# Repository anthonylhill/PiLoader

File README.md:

# PiZero Adapter for Lee Hart's Membership Card
### Project Web Page :  [ http://anthonylhill.github.io ](http://anthonylhill.github.io)
<table> 
    <tr>
        <td>System</td><td>Lee Hart's Membership Card</td>
    </tr>    
    <tr>
        <td>Processor</td><td>CDP1802 1.8 or 4 MHz</td>
    </tr>
    <tr>
        <td>Raspberry Pi</td><td>Zero,  Zero W, Zero 2 W</td>
    </tr>
    <tr>
        <td>Software</td><td>1802 Loader Program</td>
    </tr>
</table>

Software README.TXT :   https://github.com/anthonylhill/PiLoader/blob/main/Software/README.TXT </br>
<B>Tags</B> : CDP1802 eclectic retro mishmash fusion retro-futurism anachronism

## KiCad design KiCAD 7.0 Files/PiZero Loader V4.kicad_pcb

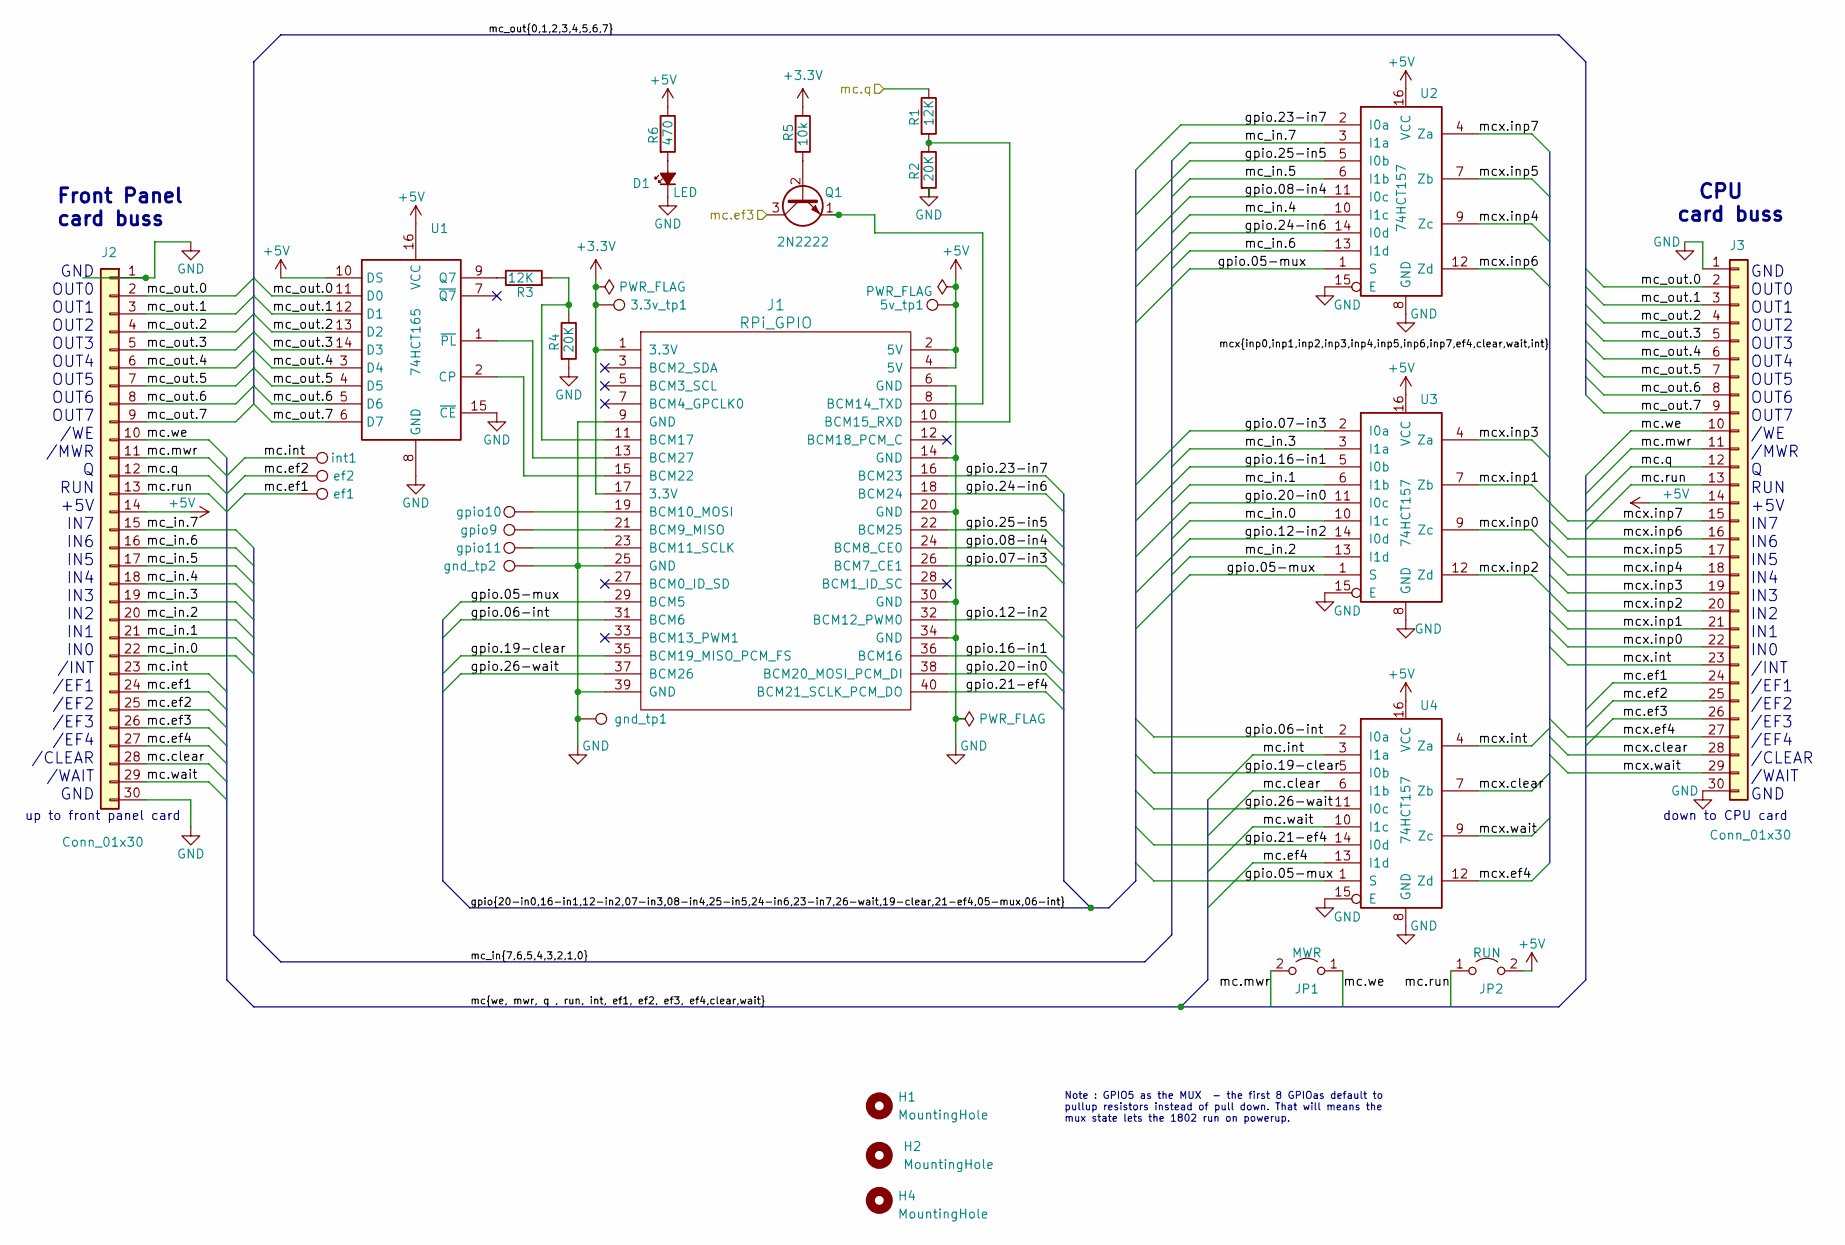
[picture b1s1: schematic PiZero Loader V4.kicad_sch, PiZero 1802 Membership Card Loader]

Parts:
3.3v_tp1, 5v_tp1: TestPoint; TestPoint_THTPad_D2.0mm_Drill1.0mm
D1: LED; PinHeader_1x02_P2.54mm_Vertical
H1, H2, H4: MountingHole; MountingHole_3.2mm_M3
J1: RPi_GPIO; Raspberry_Pi_Zero_Socketed_THT_FaceDown_MountingHoles
J2: Conn_01x30; PinHeader_1x30_P2.54mm_Vertical
J3: Conn_01x30; PinSocket_1x30_P2.54mm_Vertical
JP1: MWR; PinHeader_1x02_P2.54mm_Vertical
JP2: RUN; PinHeader_1x02_P2.54mm_Vertical
Q1: 2N2222; TO-92_Inline
R1, R3: 12K; R_Axial_DIN0207_L6.3mm_D2.5mm_P10.16mm_Horizontal
R2, R4: 20K; R_Axial_DIN0207_L6.3mm_D2.5mm_P10.16mm_Horizontal
R5: 10k; R_Axial_DIN0207_L6.3mm_D2.5mm_P10.16mm_Horizontal
R6: 470; R_Axial_DIN0207_L6.3mm_D2.5mm_P10.16mm_Horizontal
U1: 74HCT165; DIP-16_W7.62mm_Socket
U2, U3, U4: 74HCT157; DIP-16_W7.62mm_Socket
ef1, ef2: TestPoint; TestPoint_THTPad_D2.0mm_Drill1.0mm
gnd_tp1: TestPoint; TestPoint_THTPad_D2.0mm_Drill1.0mm
gnd_tp2: TestPoint; TestPoint_THTPad_2.0x2.0mm_Drill1.0mm
gpio9, gpio10, gpio11: TestPoint; TestPoint_THTPad_D2.0mm_Drill1.0mm
int1: TestPoint; TestPoint_THTPad_D2.0mm_Drill1.0mm

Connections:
+3.3V: 3.3v_tp1.1, J1.1 (3.3V), J1.17 (3.3V), R5.2
+5V: 5v_tp1.1, J1.2 (5V), J1.4 (5V), J2.14, J3.14, JP2.2 (B), R6.1, U1.10 (DS), U1.16 (VCC), U2.16 (VCC), U3.16 (VCC), U4.16 (VCC)
/gpio.05-mux: J1.29 (BCM5), U2.1 (S), U3.1 (S), U4.1 (S)
/gpio.06-int: J1.31 (BCM6), U4.2 (I0a)
/gpio.07-in3: J1.26 (BCM7_CE1), U3.2 (I0a)
/gpio.08-in4: J1.24 (BCM8_CE0), U2.11 (I0c)
/gpio.12-in2: J1.32 (BCM12_PWM0), U3.14 (I0d)
/gpio.16-in1: J1.36 (BCM16), U3.5 (I0b)
/gpio.19-clear: J1.35 (BCM19_MISO_PCM_FS), U4.5 (I0b)
/gpio.20-in0: J1.38 (BCM20_MOSI_PCM_DI), U3.11 (I0c)
/gpio.21-ef4: J1.40 (BCM21_SCLK_PCM_DO), U4.14 (I0d)
/gpio.23-in7: J1.16 (BCM23), U2.2 (I0a)
/gpio.24-in6: J1.18 (BCM24), U2.14 (I0d)
/gpio.25-in5: J1.22 (BCM25), U2.5 (I0b)
/gpio.26-wait: J1.37 (BCM26), U4.11 (I0c)
/mc.clear: J2.28, U4.6 (I1b)
/mc.ef1: J2.24, J3.24, ef1.1
/mc.ef2: J2.25, J3.25, ef2.1
/mc.ef3: J2.26, J3.26, Q1.3 (C)
/mc.ef4: J2.27, U4.13 (I1d)
/mc.int: J2.23, U4.3 (I1a), int1.1
/mc.mwr: J2.11, J3.11, JP1.2 (B)
/mc.q: J2.12, J3.12, R1.1
/mc.run: J2.13, J3.13, JP2.1 (A)
/mc.wait: J2.29, U4.10 (I1c)
/mc.we: J2.10, J3.10, JP1.1 (A)
/mc_in.0: J2.22, U3.10 (I1c)
/mc_in.1: J2.21, U3.6 (I1b)
/mc_in.2: J2.20, U3.13 (I1d)
/mc_in.3: J2.19, U3.3 (I1a)
/mc_in.4: J2.18, U2.10 (I1c)
/mc_in.5: J2.17, U2.6 (I1b)
/mc_in.6: J2.16, U2.13 (I1d)
/mc_in.7: J2.15, U2.3 (I1a)
/mc_out.0: J2.2, J3.2, U1.11 (D0)
/mc_out.1: J2.3, J3.3, U1.12 (D1)
/mc_out.2: J2.4, J3.4, U1.13 (D2)
/mc_out.3: J2.5, J3.5, U1.14 (D3)
/mc_out.4: J2.6, J3.6, U1.3 (D4)
/mc_out.5: J2.7, J3.7, U1.4 (D5)
/mc_out.6: J2.8, J3.8, U1.5 (D6)
/mc_out.7: J2.9, J3.9, U1.6 (D7)
/mcx.clear: J3.28, U4.7 (Zb)
/mcx.ef4: J3.27, U4.12 (Zd)
/mcx.inp0: J3.22, U3.9 (Zc)
/mcx.inp1: J3.21, U3.7 (Zb)
/mcx.inp2: J3.20, U3.12 (Zd)
/mcx.inp3: J3.19, U3.4 (Za)
/mcx.inp4: J3.18, U2.9 (Zc)
/mcx.inp5: J3.17, U2.7 (Zb)
/mcx.inp6: J3.16, U2.12 (Zd)
/mcx.inp7: J3.15, U2.4 (Za)
/mcx.int: J3.23, U4.4 (Za)
/mcx.wait: J3.29, U4.9 (Zc)
GND: D1.1 (K), J1.6 (GND), J1.9 (GND), J1.14 (GND), J1.20 (GND), J1.25 (GND), J1.30 (GND), J1.34 (GND), J1.39 (GND), J2.1, J2.30, J3.1, J3.30, R2.2, R4.2, U1.8 (GND), U1.15 (~CE), U2.8 (GND), U2.15 (E), U3.8 (GND), U3.15 (E), U4.8 (GND), U4.15 (E), gnd_tp1.1, gnd_tp2.1
unnamed: D1.2 (A), R6.2
unnamed: J1.21 (BCM9_MISO), gpio9.1
unnamed: J1.19 (BCM10_MOSI), gpio10.1
unnamed: J1.23 (BCM11_SCLK), gpio11.1
unnamed: J1.8 (BCM14_TXD), Q1.1 (E)
unnamed: J1.10 (BCM15_RXD), R1.2, R2.1
unnamed: J1.11 (BCM17), R3.2, R4.1
unnamed: J1.15 (BCM22), U1.2 (CP)
unnamed: J1.13 (BCM27), U1.1 (~PL)
unnamed: Q1.2 (B), R5.1
unnamed: R3.1, U1.9 (Q7)

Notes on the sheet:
Front Panel card buss
GND OUT0 OUT1 OUT2 OUT3 OUT4 OUT5 OUT6 OUT7 /WE /MWR Q RUN +5V IN7 IN6 IN5 IN4 IN3 IN2 IN1 IN0 /INT /EF1 /EF2 /EF3 /EF4 /CLEAR /WAIT GND
Note : GPIO5 as the MUX - the first 8 GPIOas default to pullup resistors instead of pull down. That will means the mux state lets the 1802 run on powerup.
CPU card buss
up to front panel card
down to CPU card

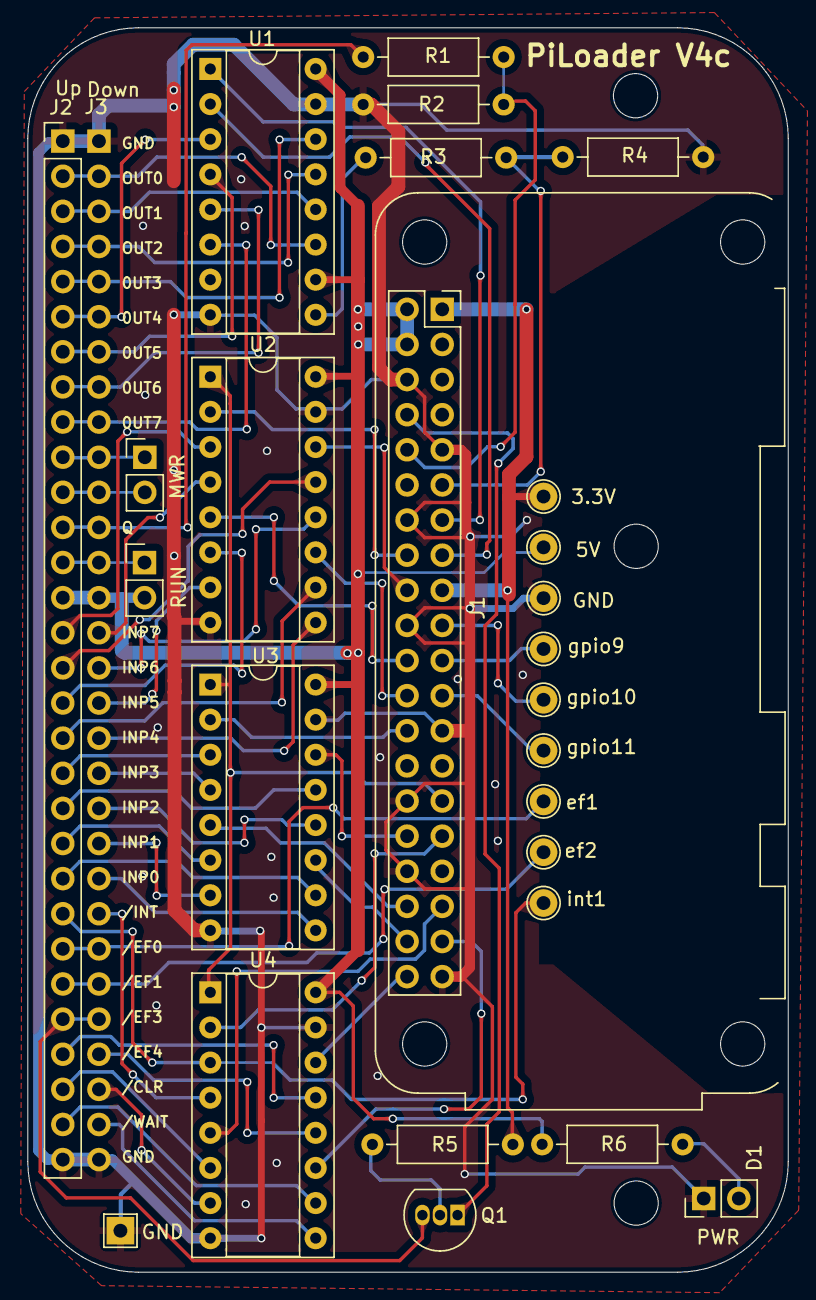
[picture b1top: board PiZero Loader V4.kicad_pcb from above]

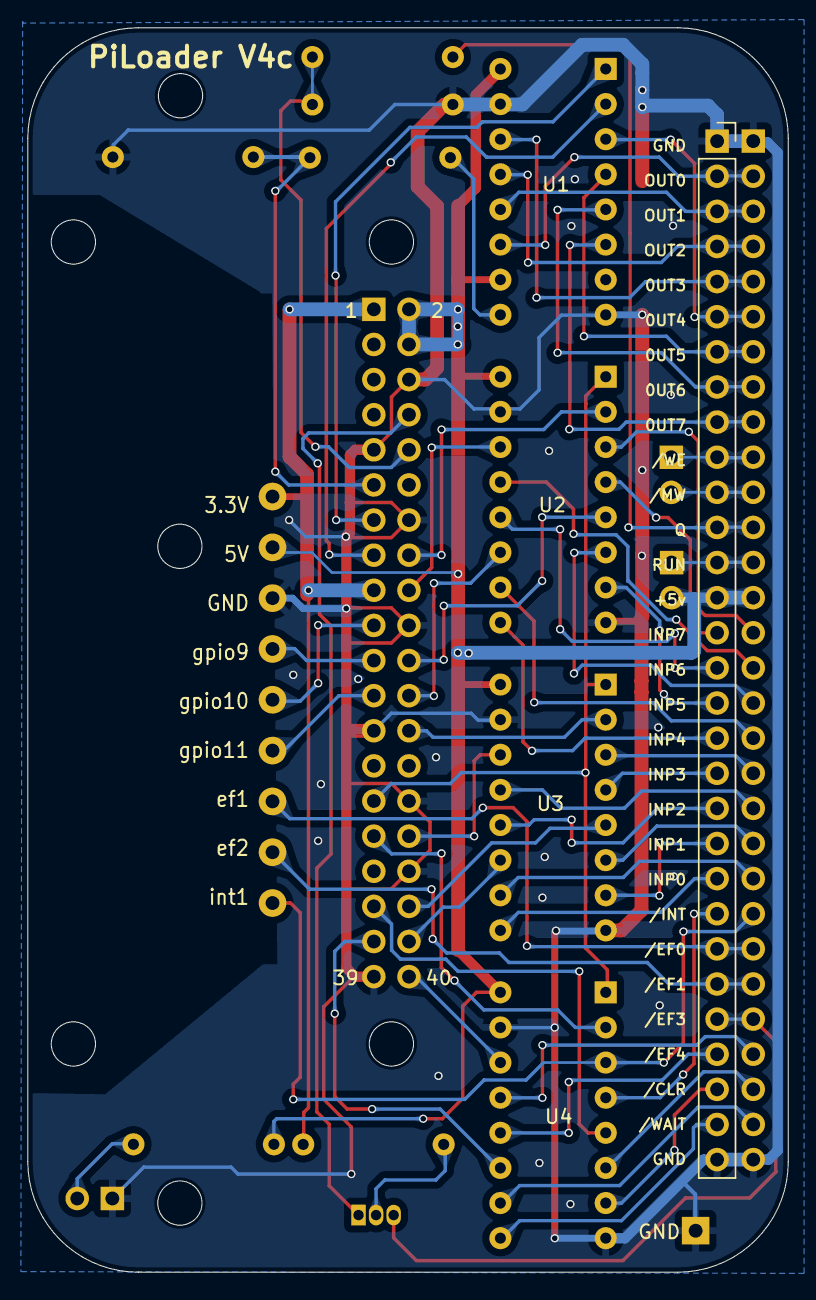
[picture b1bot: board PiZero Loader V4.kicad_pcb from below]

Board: 2 copper layers, 55.0 x 90.0 mm, 30 parts (2 on the bottom side), 66 nets.

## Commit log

2023-06-16 initial setup
2023-06-16 added KiCAD files
2023-06-16 added code for loader program
2023-06-16 added dev screenshot
2023-06-16 converted screenshot from png to jpg
2023-06-16 photo problems
2023-06-16 added simple scanner code
2023-06-16 added a minicom default settings file
2023-06-16 Revert "photo problems"
    This reverts commit c5aadec0819fcb2125e6a5059fd9f22f45d96ed8.
2023-06-16 photos for README.md
    This reverts commit 313a9934627228dc030915c124672213eded6270.
2023-06-16 updated photos
2023-06-16 added local mode photo
2023-06-17 updated BOM and Assembly Instructions
2023-06-18 removed text and photos duplicated on project website
    see https://anthonylhill.github.io/
2023-10-20 missing files
    added loader_gpio.h and loader_utils.h
2023-10-20 additional source files
    - added a small README file to the software folder
    - added gpio bit test programs
    - added some example 1802 assembler files
2023-10-20 Update 1802load.c
    - fixed typo in previous change
2023-10-20 Update README.TXT
    - added note about only pigpio being fully tested with 1802load.c
2023-10-20 Update BOM and Assembly Instructions.pdf
    added a couple of notes to the software section
2023-11-02 Update makefile
    deleted reference to idiot monitor in the makefile
2023-11-02 gpio related code cleanup
    removed unused gpio access methods and merged loader_utils.h into the gpio_get and gpio_set code
2023-11-02 updated makefile to remove unused include files
2023-11-02 added a clean option to the makefile
    clean option deletes all .LST files and touches all source files to force a recompile or assemble on next invocation of make
2023-11-03 added a note about /ON grounding
    the RUN jumper on the adapter card will bypass the front panel /ON signal and always send a RUN signal to the CPU card. However on front panels rev L and beyond, you still need the jumper on the fron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
2023-12-04 1802load updated
    1802load now supports loading and running code at addresses other 0x0000
2023-12-05 added -x switch
    Added -x to cause loader to simply jump to the load/execute address without loading any code. Useful for testing or jumping to ROM in high memory.
2023-12-05 updated fpr ve 3/5
2023-12-05 bug fix and misc cleanups
    fixed sigHandler: Unhandled signal 11, terminating crash introduced in previous update
2023-12-09 added a warning
    added warning to comments about this version of the loader overwriting all memory between 0x0000 and the load address when loading a file
2023-12-14 update functionality for 1802load
    updated 1802load to enable loading binary files anywhere in memory without clobbering all the locations below that load and 0x000
2023-12-15 minor update to build instructions
    added complete command syntax for 1802load utility program
2023-12-24 added load without execute
    - added a switch to allow loading only - processor is left in LOAD mode and not put into RUN mode after the load
    - general cleanup of the command line switches with some reassignment of functionality
    - added a "stop the 1802" mode
2023-12-24 UI improvements
    - added user confirmation in verbose mode before proceeding
    - added switch to default user answer to "Yes"
    - upgrade checking of hex input values to limit valid inputs to 4 characters
2023-12-24 Update README.md
    added link to software README.TXT file
2023-12-24 UI updates
    - reworked verbose mode to better describe actions that will be taken
2023-12-24 white space cleanup
    -tidy tidy tidy
2023-12-24 file name change
    - renamed bit bank serial asm file
2023-12-24 Delete Software/1802_bit_bang_serial.asm
    renamed
2023-12-24 renamed file
2023-12-24 updated makefile
2023-12-24 Update BOM and Assembly Instructions.pdf
    add introduction section - mostly borrowed from project's github html webpage
2023-12-25 added warning not to install JP1
    if JP1 is installed and the front panel READ/WRTIE swtich is set to the READ position then the 1802 /MWR pin gets shorted to +5V
2023-12-26 JP1 & JP2 assembly instructions changed
    = added wording to the assembly instructions and schematic stating that JP1 and JP2 are only for use with a standalone CPU card (i.e. when not using the MC Front Panel card).
